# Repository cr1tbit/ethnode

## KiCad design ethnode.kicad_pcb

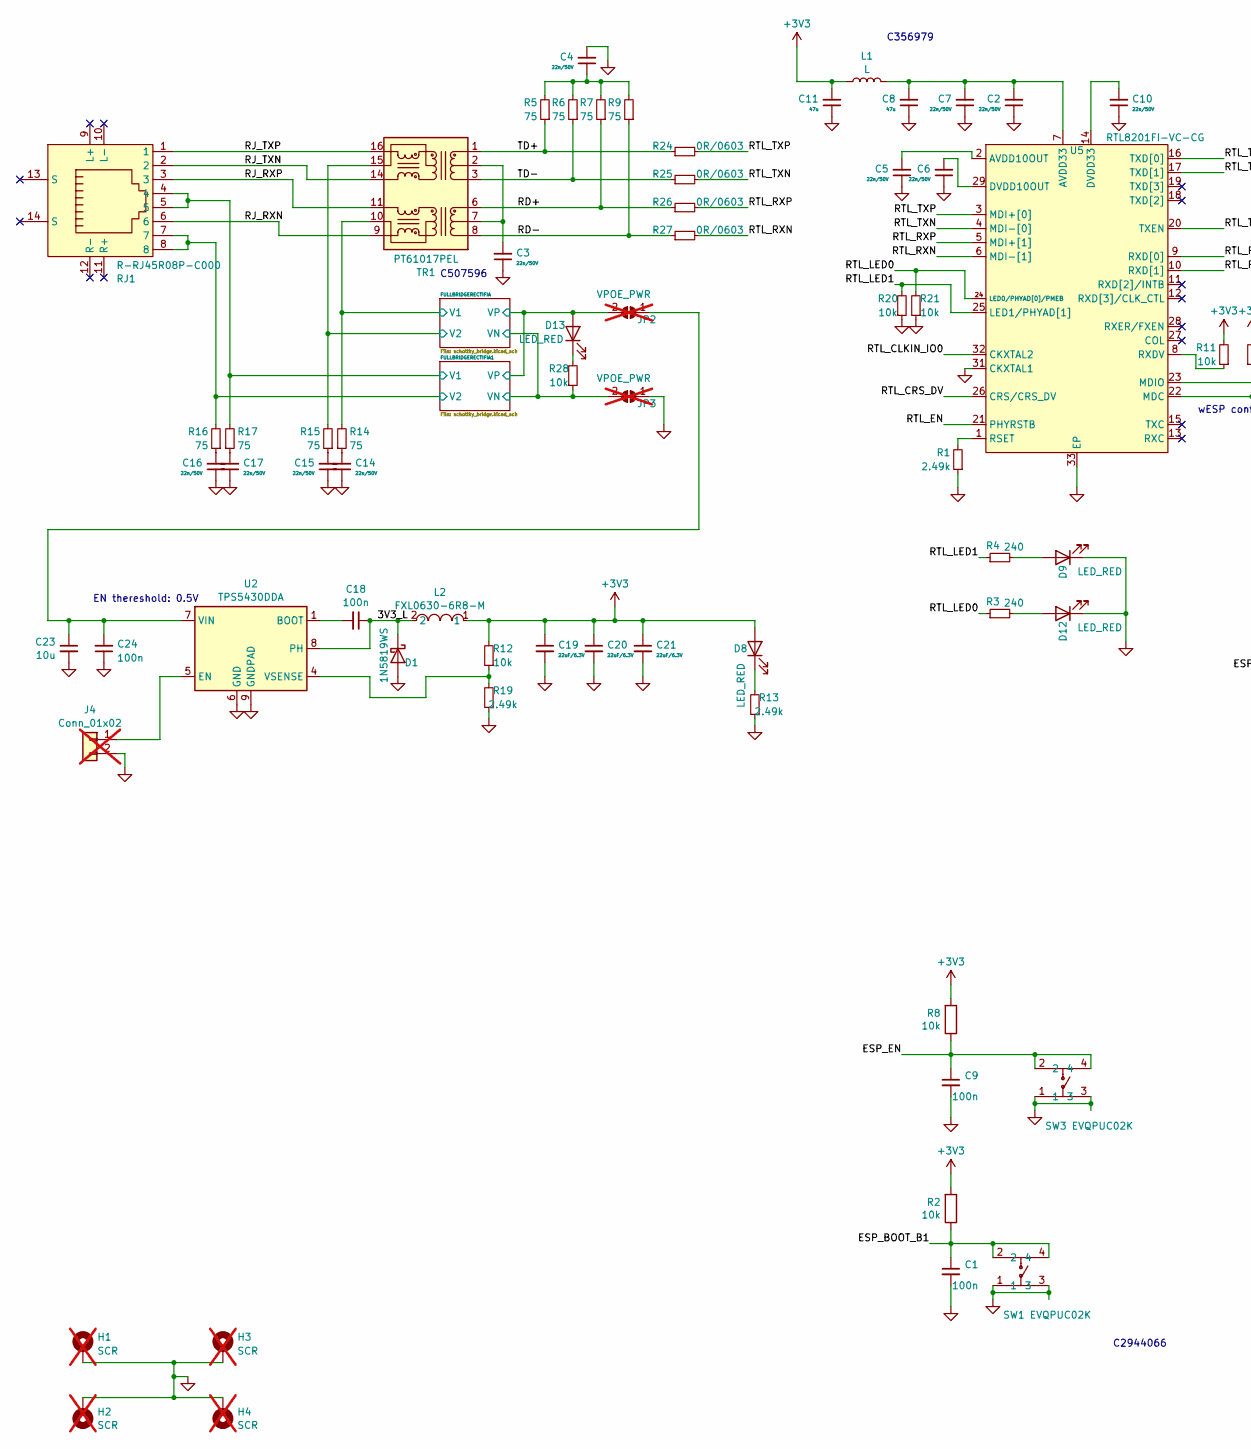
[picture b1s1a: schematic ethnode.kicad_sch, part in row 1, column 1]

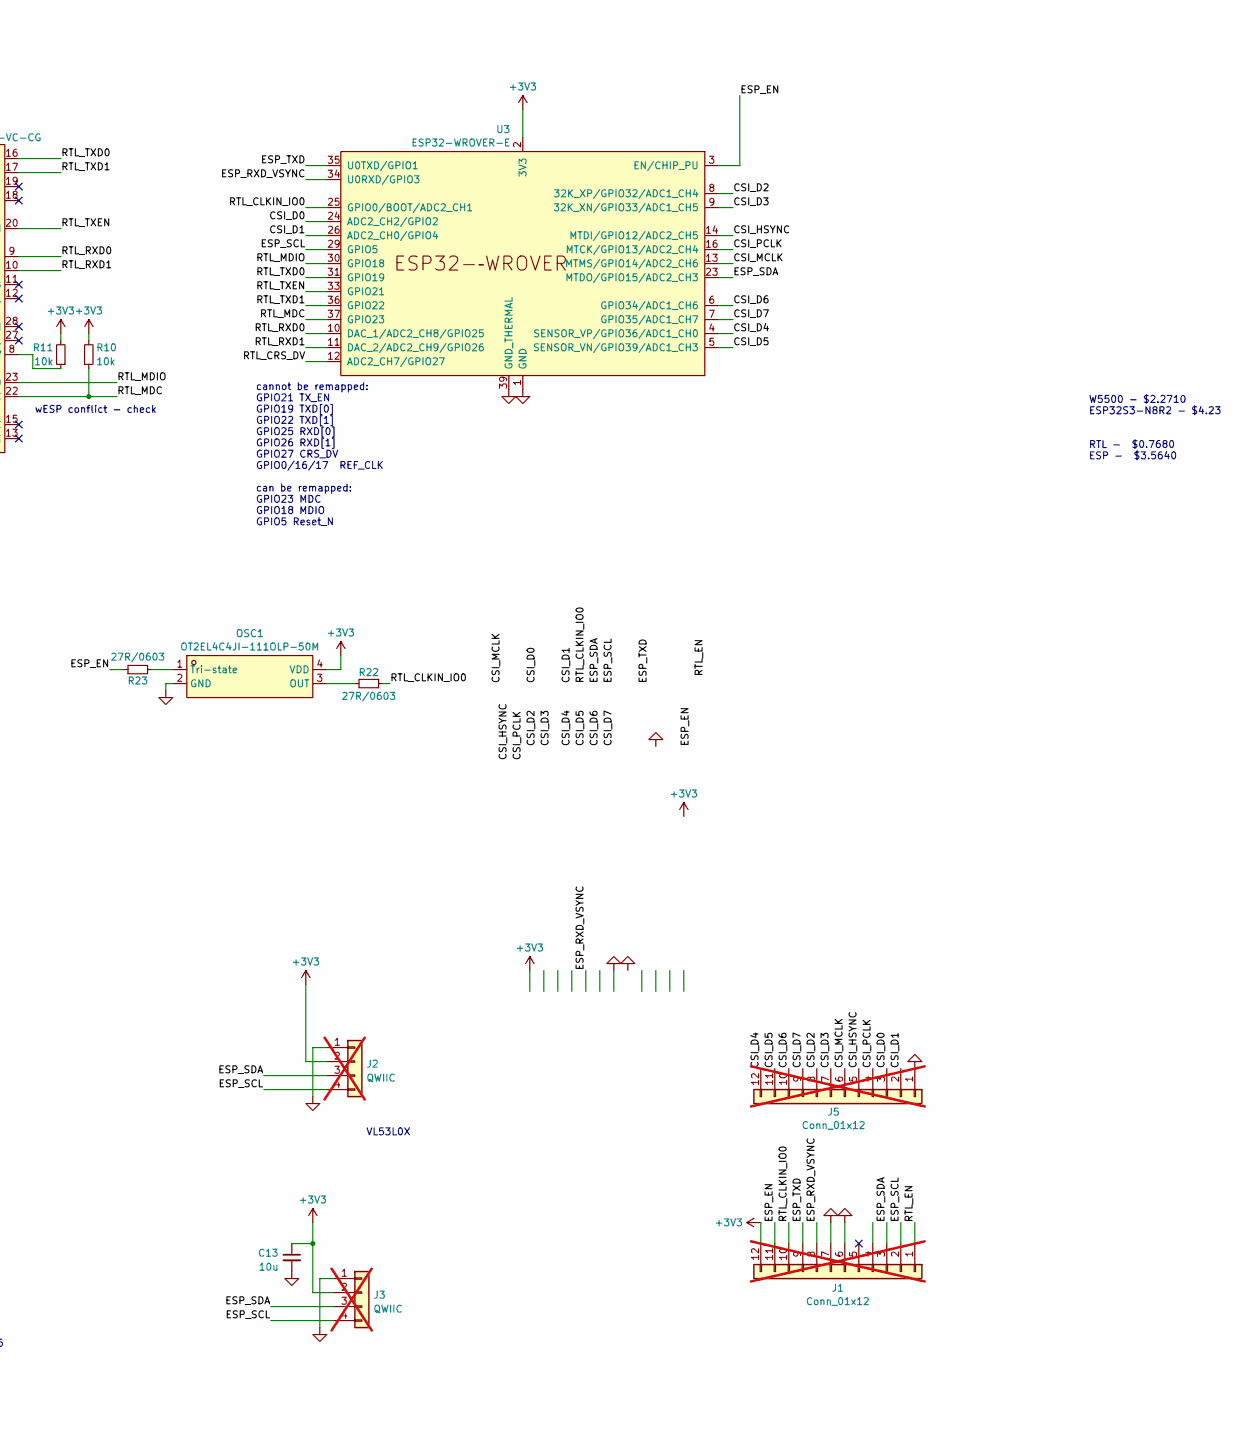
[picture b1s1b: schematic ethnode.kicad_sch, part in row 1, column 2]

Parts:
C1, C9, C18, C24: 100n; C_0402_1005Metric
C2, C3, C4, C5, C6, C7, C10, C14, C15, C16, C17: 22n/50V; C_0402_1005Metric
C8, C11: 47u; C_0805_2012Metric
C13, C23: 10u; C_0603_1608Metric
C19, C20, C21: 22uF/6.3V; C_0603_1608Metric
D1: 1N5819WS; D_SOD-323
D8, D9, D12, D13: LED_RED; LED_0603_1608Metric
H1, H2, H3, H4: SCR; MountingHole_2.2mm_M2_Pad_TopOnly; not fitted
J1, J5: Conn_01x12; PinHeader_1x12_P2.54mm_Vertical; not fitted
J2, J3: QWIIC; JST_SH_SM04B-SRSS-TB_1x04-1MP_P1.00mm_Horizontal; not fitted
J4: Conn_01x02; PinHeader_1x02_P2.54mm_Vertical; not fitted
JP2, JP3: VPOE_PWR; SolderJumper-2_P1.3mm_Open_TrianglePad1.0x1.5mm; not fitted
L1: L; L_0603_1608Metric
L2: FXL0630-6R8-M; IND-SMD_L7.0-W6.6; LCSC Part C167221
OSC1: OT2EL4C4JI-111OLP-50M; OSC-SMD_4P-L3.2-W2.5-BL; LCSC Part C5203552
R1, R13, R19: 2.49k; R_0402_1005Metric
R2, R8, R10, R11, R12, R20, R21, R28: 10k; R_0402_1005Metric
R3, R4: 240; R_0402_1005Metric
R5, R6, R7, R9, R14, R15, R16, R17: 75; R_0402_1005Metric
R22, R23: 27R/0603; R_0603_1608Metric_Pad0.98x0.95mm_HandSolder
R24, R25, R26, R27: 0R/0603; R_0603_1608Metric_Pad0.98x0.95mm_HandSolder
RJ1: R-RJ45R08P-C000; RJ45-TH_R-RJ45R08P-C000; LCSC Part C386757
SW1, SW3: EVQPUC02K; SW-SMD_EVQPUD02K
TR1: PT61017PEL; Transformer_Ethernet_Bourns_PT61017PEL
U2: TPS5430DDA; TI_SO-PowerPAD-8_ThermalVias
U3: ESP32-WROVER-E
U5: RTL8201FI-VC-CG; QFN-32_L5.0-W5.0-P0.50-BL-EP3.4; LCSC Part C2763557

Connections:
+3V3: C11.2, C13.1, C19.1, C20.1, C21.1, D8.2 (A), J1.12, J2.2, J3.2, L1.1, L2.1, OSC1.4 (VDD), R2.2, R8.2, R10.2, R11.2, R12.2, U3.2 (3V3)
/3V3_L: C18.1, D1.1 (K), L2.2, U2.8 (PH)
/CSI_D0: J5.3, U3.24 (ADC2_CH2/GPIO2)
/CSI_D1: J5.2, U3.26 (ADC2_CH0/GPIO4)
/CSI_D2: J5.8, U3.8 (32K_XP/GPIO32/ADC1_CH4)
/CSI_D3: J5.7, U3.9 (32K_XN/GPIO33/ADC1_CH5)
/CSI_D4: J5.12, U3.4 (SENSOR_VP/GPIO36/ADC1_CH0)
/CSI_D5: J5.11, U3.5 (SENSOR_VN/GPIO39/ADC1_CH3)
/CSI_D6: J5.10, U3.6 (GPIO34/ADC1_CH6)
/CSI_D7: J5.9, U3.7 (GPIO35/ADC1_CH7)
/CSI_HSYNC: J5.5, U3.14 (MTDI/GPIO12/ADC2_CH5)
/CSI_MCLK: J5.6, U3.13 (MTMS/GPIO14/ADC2_CH6)
/CSI_PCLK: J5.4, U3.16 (MTCK/GPIO13/ADC2_CH4)
/ESP_BOOT_B1: C1.1, R2.1, SW1.2, SW1.4
/ESP_EN: C9.1, J1.11, R8.1, R23.1, SW3.2, SW3.4, U3.3 (EN/CHIP_PU)
/ESP_RXD_VSYNC: J1.8, U3.34 (U0RXD/GPIO3)
/ESP_SCL: J1.2, J2.4, J3.4, U3.29 (GPIO5)
/ESP_SDA: J1.3, J2.3, J3.3, U3.23 (MTDO/GPIO15/ADC2_CH3)
/ESP_TXD: J1.9, U3.35 (U0TXD/GPIO1)
/FULLBRIDGERECTIFIA1/V1: R17.2, RJ1.4, RJ1.5; also elsewhere on the board
/FULLBRIDGERECTIFIA1/V2: R16.2, RJ1.7, RJ1.8; also elsewhere on the board
/FULLBRIDGERECTIFIA/V1: R14.2, TR1.10 (C_RX); also elsewhere on the board
/FULLBRIDGERECTIFIA/V2: R15.2, TR1.15 (C_TX); also elsewhere on the board
/FULLBRIDGERECTIFIA/VN: JP3.2 (B), R28.1; also elsewhere on the board
/FULLBRIDGERECTIFIA/VP: D13.2 (A), JP2.2 (B); also elsewhere on the board
/RD+: R7.1, R26.1, TR1.6 (RD+)
/RD-: R9.1, R27.1, TR1.8 (RD-)
/RJ_RXN: RJ1.6, TR1.9 (RX-)
/RJ_RXP: RJ1.3, TR1.11 (RX+)
/RJ_TXN: RJ1.2, TR1.14 (TX-)
/RJ_TXP: RJ1.1, TR1.16 (TX+)
/RTL_CLKIN_IO0: J1.10, R22.1, U3.25 (GPIO0/BOOT/ADC2_CH1), U5.32 (CKXTAL2)
/RTL_CRS_DV: U3.12 (ADC2_CH7/GPIO27), U5.26 (CRS/CRS_DV)
/RTL_EN: J1.1, U5.21 (PHYRSTB)
/RTL_LED0: R3.1, R21.2, U5.24 (LED0/PHYAD[0]/PMEB)
/RTL_LED1: R4.1, R20.2, U5.25 (LED1/PHYAD[1])
/RTL_MDC: R10.1, U3.37 (GPIO23), U5.22 (MDC)
/RTL_MDIO: U3.30 (GPIO18), U5.23 (MDIO)
/RTL_RXD0: U3.10 (DAC_1/ADC2_CH8/GPIO25), U5.9 (RXD[0])
/RTL_RXD1: U3.11 (DAC_2/ADC2_CH9/GPIO26), U5.10 (RXD[1])
/RTL_RXN: R27.2, U5.6 (MDI-[1])
/RTL_RXP: R26.2, U5.5 (MDI+[1])
/RTL_TXD0: U3.31 (GPIO19), U5.16 (TXD[0])
/RTL_TXD1: U3.36 (GPIO22), U5.17 (TXD[1])
/RTL_TXEN: U3.33 (GPIO21), U5.20 (TXEN)
/RTL_TXN: R25.2, U5.4 (MDI-[0])
/RTL_TXP: R24.2, U5.3 (MDI+[0])
/TD+: R5.1, R24.1, TR1.1 (TD+)
/TD-: R6.1, R25.1, TR1.3 (TD-)
GND: C1.2, C2.1, C3.1, C4.2, C5.1, C6.1, C7.1, C8.1, C9.2, C10.1, C11.1, C13.2, C14.1, C15.1, C16.1, C17.1, C19.2, C20.2, C21.2, C23.2, C24.1, D1.2 (A), D9.1 (K), D12.1 (K), H1.1, H2.1, H3.1, H4.1, J1.6, J1.7, J2.1, J3.1, J4.2, J5.1, JP3.1 (A), OSC1.2 (GND), R1.1, R13.1, R19.1, R20.1, R21.1, SW1.1, SW1.3, SW3.1, SW3.3, U2.6 (GND), U2.9 (GNDPAD), U3.1 (GND), U3.15 (GND), U3.38 (GND), U3.39 (GND_THERMAL), U5.31 (CKXTAL1), U5.33 (EP)
unnamed: C2.2, C7.2, C8.2, L1.2, U5.7 (AVDD33), U5.30 (AVDD33)
unnamed: C4.1, R5.2, R6.2, R7.2, R9.2
unnamed: C14.2, R14.1
unnamed: C15.2, R15.1
unnamed: C16.2, R16.1
unnamed: C17.2, R17.1
unnamed: D8.1 (K), R13.2
unnamed: D9.2 (A), R4.2
unnamed: D12.2 (A), R3.2
unnamed: D13.1 (K), R28.2
unnamed: J4.1, U2.5 (EN)
unnamed: C23.1, C24.2, JP2.1 (A), U2.7 (VIN)
unnamed: OSC1.3 (OUT), R22.2
unnamed: OSC1.1 (Tri-state), R23.2
unnamed: C3.2, TR1.2 (C_TD), TR1.7 (C_RD)
unnamed: C18.2, U2.1 (BOOT)
unnamed: R12.1, R19.2, U2.4 (VSENSE)
unnamed: C5.2, U5.2 (AVDD10OUT)
unnamed: C6.2, U5.29 (DVDD10OUT)
unnamed: C10.2, U5.14 (DVDD33)
unnamed: R1.2, U5.1 (RSET)
unnamed: R11.1, U5.8 (RXDV)

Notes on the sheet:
wESP conflict - check
cannot be remapped: GPIO21 TX_EN GPIO19 TXD[0] GPIO22 TXD[1] GPIO25 RXD[0] GPIO26 RXD[1] GPIO27 CRS_DV GPIO0/16/17 REF_CLK can be remapped: GPIO23 MDC GPIO18 MDIO GPIO5 Reset_N
C2944066
C356979
VL53L0X
W5500 - $2.2710 ESP32S3-N8R2 - $4.23 RTL - $0.7680 ESP - $3.5640
EN thereshold: 0.5V
C507596

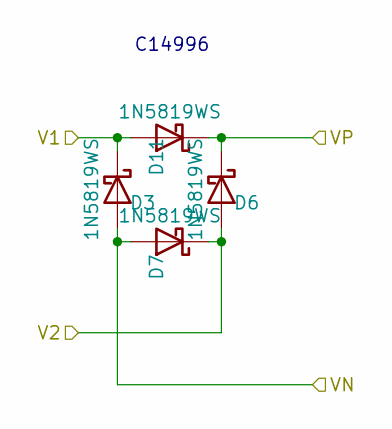
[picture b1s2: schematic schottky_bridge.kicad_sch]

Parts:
D3, D6, D7, D11: 1N5819WS; D_SOD-323

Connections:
/FULLBRIDGERECTIFIA1/V1: D3.1 (K), D11.2 (A); also elsewhere on the board
/FULLBRIDGERECTIFIA1/V2: D6.2 (A), D7.1 (K); also elsewhere on the board
/FULLBRIDGERECTIFIA/VN: D3.2 (A), D7.2 (A); also elsewhere on the board
/FULLBRIDGERECTIFIA/VP: D6.1 (K), D11.1 (K); also elsewhere on the board

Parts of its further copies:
D2, D4, D5, D10: 1N5819WS; D_SOD-323

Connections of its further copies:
/FULLBRIDGERECTIFIA/V1: D2.1 (K), D10.2 (A); also elsewhere on the board
/FULLBRIDGERECTIFIA/V2: D4.2 (A), D5.1 (K); also elsewhere on the board
/FULLBRIDGERECTIFIA/VN: D2.2 (A), D5.2 (A); also elsewhere on the board
/FULLBRIDGERECTIFIA/VP: D4.1 (K), D10.1 (K); also elsewhere on the board

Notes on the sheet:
C14996

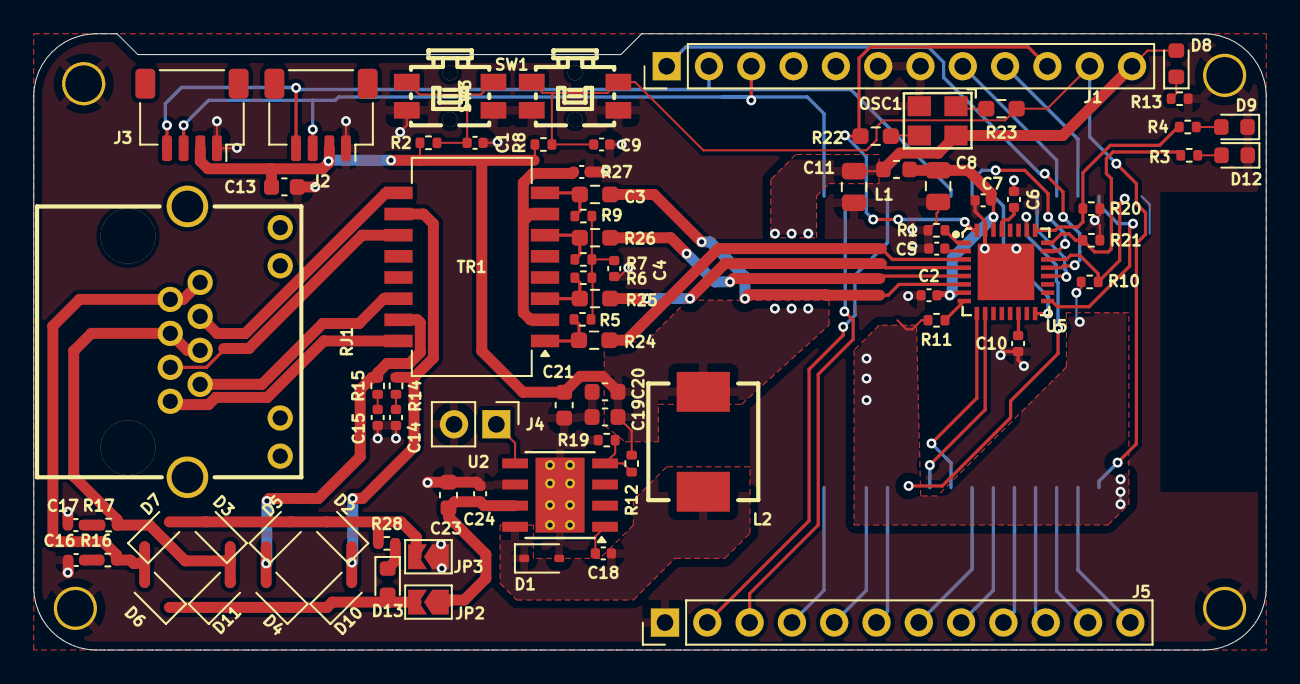
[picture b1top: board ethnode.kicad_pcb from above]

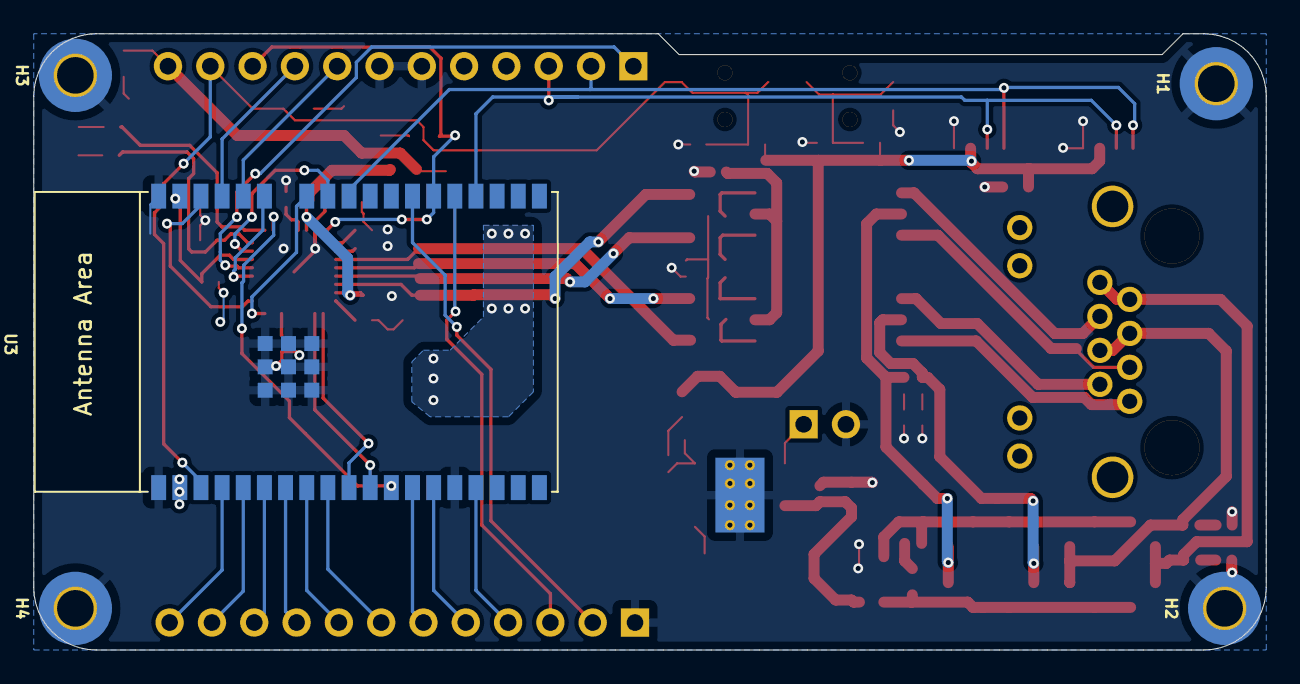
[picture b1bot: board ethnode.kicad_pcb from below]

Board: 2 copper layers, 74.0 x 37.0 mm, 83 parts (5 on the bottom side), 72 nets.

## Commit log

2024-07-21 add files
2024-09-25 add schematic, testshield stub
